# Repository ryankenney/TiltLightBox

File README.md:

TiltLightBox
====================

About
--------------------

TiltLightBox is a hardware/software platform we developed for an ( link) interactive exhibit at Burning Man 2015. At its core, TiltLightBox is just a bunch of durable, illuminated boxes that can detect when they're knocked over and respond with appropriate color/sound effects. They employ battery packs and cheap wifi adapters in order to centralized control of color/sound themes.

[![alt text][1]][2]

  [1]: docs/Overview_thumb.png (Overview)
  [2]: docs/Overview.png

[![alt text][3]][4]

  [3]: docs/Overview_TiltLightBox_thumb.png (TiltLightBox Unit)
  [4]: docs/Overview_TiltLightBox.png

[![alt text][5]][6]

  [5]: docs/Overview_TiltLightBox-Server_thumb.png (TiltLightBox Server)
  [6]: docs/Overview_TiltLightBox-Server.png

Index
--------------------

*  [Building the Hardware]()
	* [Wiring Diagrams](docs/Wiring Diagrams.md)
*  [Testing in Web Emulator]()
* [Deploying the TiltLightBox Software to the Arduino Boxes](docs/Arduino Setup.md) (to Arduinos)
* [Deploying the TiltLightBox Software to the Raspberry Pi Server](docs/Raspberry Pi Setup.md) (to Raspberry Pi)
* [Archive](archive/README.md)

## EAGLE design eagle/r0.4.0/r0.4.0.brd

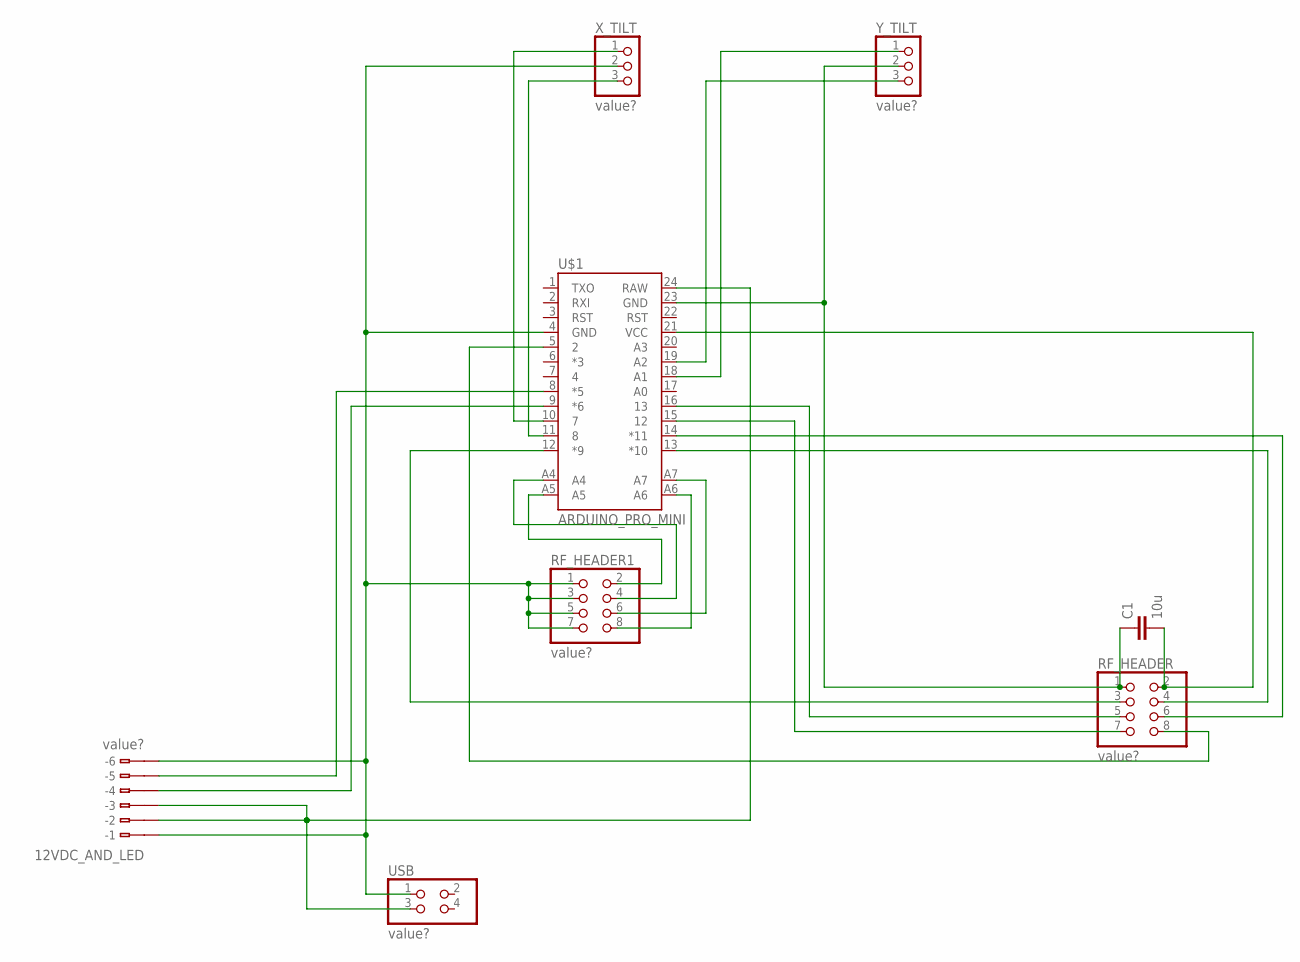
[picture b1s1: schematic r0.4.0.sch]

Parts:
12VDC_AND_LED: value?; 234-206
C1: 10u; CAP-PTH-SMALL
RF_HEADER, RF_HEADER1: value?; 2X04
U$1: ARDUINO_PRO_MINI
USB: value?; 2X02
X_TILT: value?; 1X03
Y_TILT: value?; 1X03

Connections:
unnamed: U$1.10 (7), X_TILT.1
unnamed: 12VDC_AND_LED.B1 (B-1), 12VDC_AND_LED.B6 (B-6), RF_HEADER1.1, RF_HEADER1.3, RF_HEADER1.5, RF_HEADER1.7, U$1.4 (GND), USB.1, X_TILT.2
unnamed: U$1.11 (8), X_TILT.3
unnamed: 12VDC_AND_LED.B5 (B-5), U$1.8 (*5)
unnamed: 12VDC_AND_LED.B2 (B-2), 12VDC_AND_LED.B3 (B-3), U$1.24 (RAW), USB.3
unnamed: C1.1, RF_HEADER.1, U$1.23 (GND), Y_TILT.2
unnamed: 12VDC_AND_LED.B4 (B-4), U$1.9 (*6)
unnamed: RF_HEADER1.4, U$1.A4
unnamed: U$1.19 (A2), Y_TILT.3
unnamed: RF_HEADER.3, U$1.12 (*9)
unnamed: RF_HEADER.4, U$1.13 (*10)
unnamed: RF_HEADER.6, U$1.14 (*11)
unnamed: RF_HEADER1.2, U$1.A5
unnamed: RF_HEADER1.8, U$1.A6
unnamed: RF_HEADER1.6, U$1.A7
unnamed: RF_HEADER.7, U$1.15 (12)
unnamed: RF_HEADER.5, U$1.16 (13)
unnamed: RF_HEADER.8, U$1.5 (2)
unnamed: U$1.18 (A1), Y_TILT.1
Y_TILT: C1.2, RF_HEADER.2, U$1.21 (VCC)

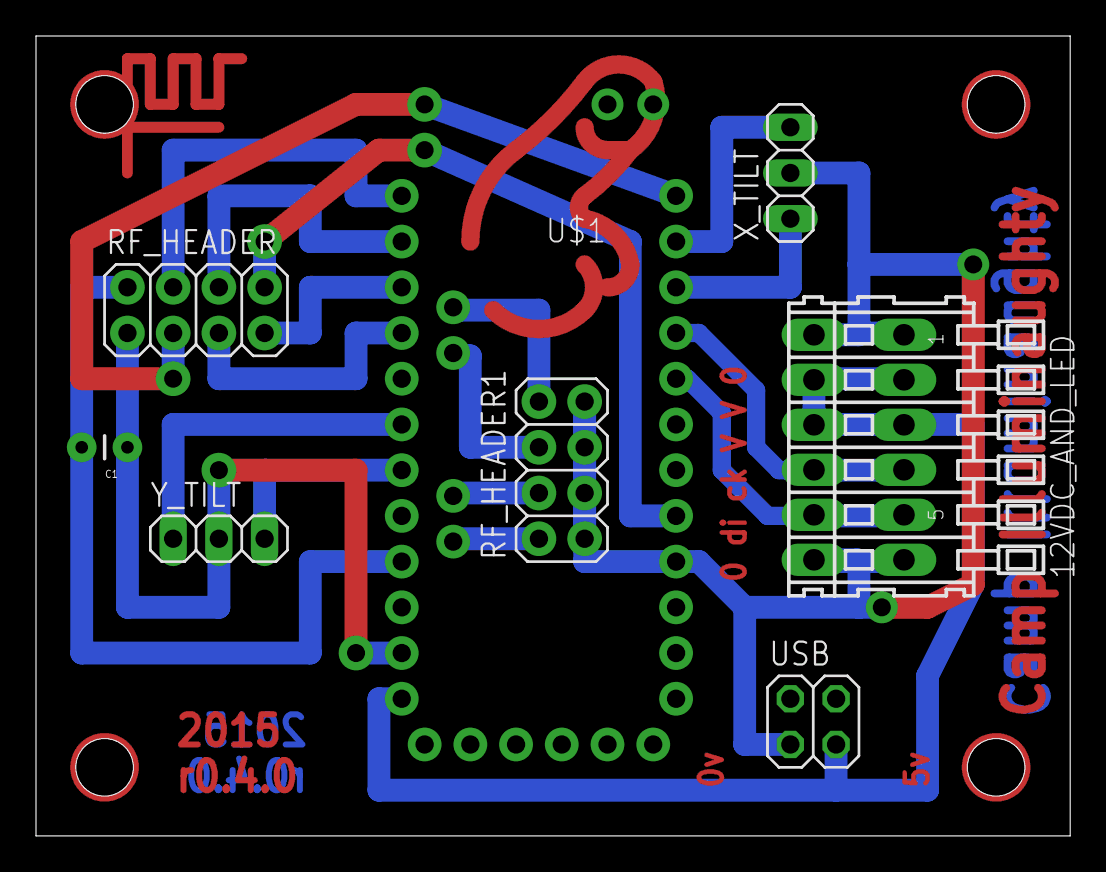
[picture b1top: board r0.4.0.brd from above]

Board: 2 copper layers, 57.5 x 44.4 mm, 8 parts (0 on the bottom side), 20 nets.

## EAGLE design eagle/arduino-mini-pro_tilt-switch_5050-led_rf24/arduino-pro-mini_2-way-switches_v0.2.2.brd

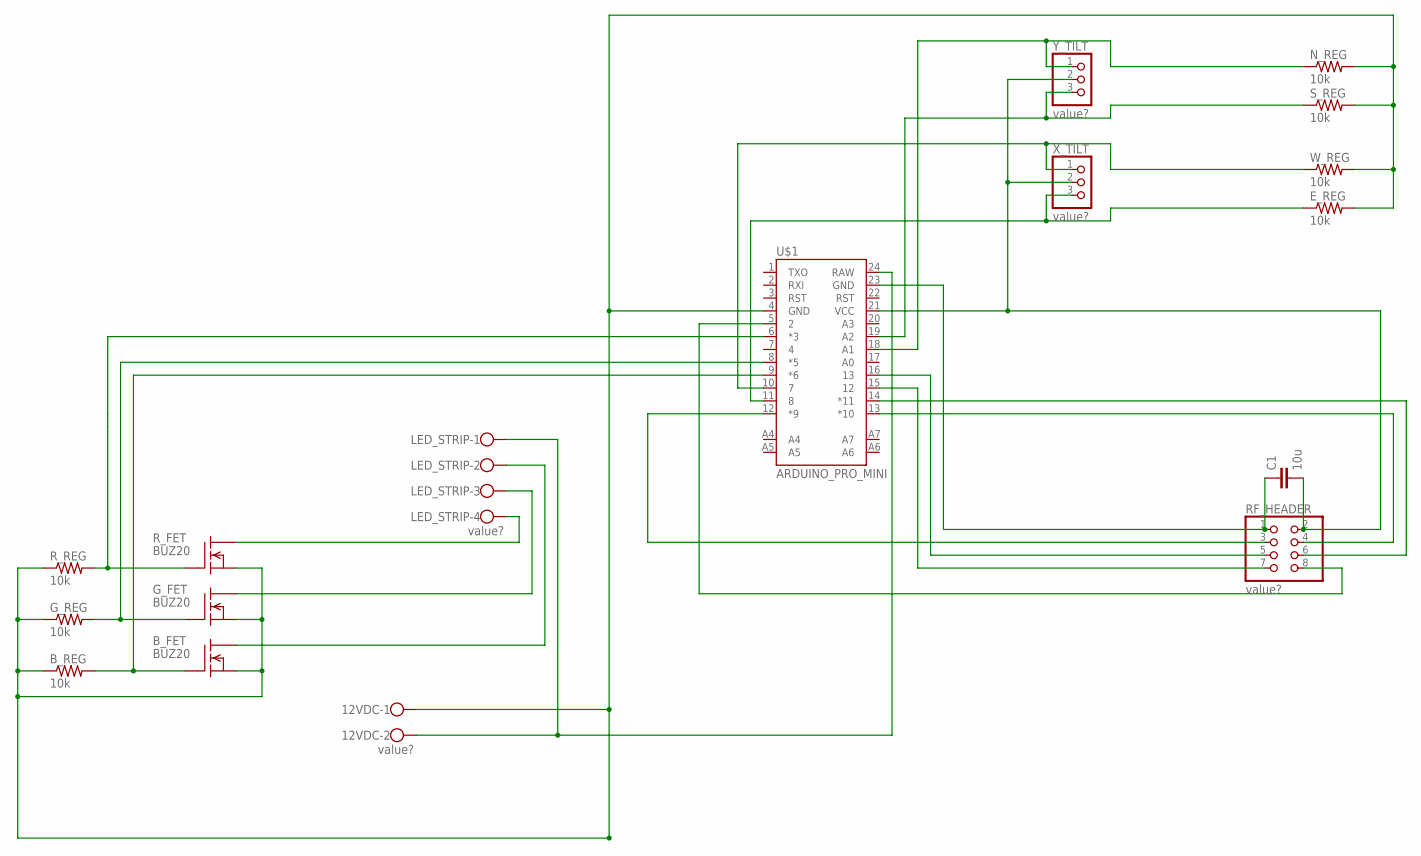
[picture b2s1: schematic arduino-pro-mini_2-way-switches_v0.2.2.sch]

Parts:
12VDC: value?; W237-102
B_FET: BUZ20; TO220
B_REG: 10k; AXIAL-0.4
C1: 10u; CAP-PTH-SMALL
E_REG: 10k; AXIAL-0.4
G_FET: BUZ20; TO220
G_REG: 10k; AXIAL-0.4
LED_STRIP: value?; W237-4
N_REG: 10k; AXIAL-0.4
RF_HEADER: value?; 2X04
R_FET: BUZ20; TO220
R_REG: 10k; AXIAL-0.4
S_REG: 10k; AXIAL-0.4
U$1: ARDUINO_PRO_MINI
W_REG: 10k; AXIAL-0.4
X_TILT: value?; 1X03
Y_TILT: value?; 1X03

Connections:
unnamed: U$1.10 (7), W_REG.P$1 (1), X_TILT.1
unnamed: B_FET.1 (G), B_REG.P$2 (2), U$1.9 (*6)
unnamed: R_FET.1 (G), R_REG.P$2 (2), U$1.6 (*3)
unnamed: G_FET.2 (D), LED_STRIP.3
unnamed: B_FET.2 (D), LED_STRIP.2
unnamed: E_REG.P$1 (1), U$1.11 (8), X_TILT.3
unnamed: LED_STRIP.4, R_FET.2 (D)
unnamed: 12VDC.2, LED_STRIP.1, U$1.24 (RAW)
unnamed: 12VDC.1, B_FET.3 (S), B_REG.P$1 (1), E_REG.P$2 (2), G_FET.3 (S), G_REG.P$1 (1), N_REG.P$2 (2), R_FET.3 (S), R_REG.P$1 (1), S_REG.P$2 (2), U$1.4 (GND), W_REG.P$2 (2)
unnamed: G_FET.1 (G), G_REG.P$2 (2), U$1.8 (*5)
unnamed: S_REG.P$1 (1), U$1.19 (A2), Y_TILT.3
unnamed: RF_HEADER.3, U$1.12 (*9)
unnamed: RF_HEADER.4, U$1.13 (*10)
unnamed: RF_HEADER.6, U$1.14 (*11)
unnamed: C1.1, RF_HEADER.1, U$1.23 (GND)
unnamed: RF_HEADER.7, U$1.15 (12)
unnamed: RF_HEADER.5, U$1.16 (13)
unnamed: RF_HEADER.8, U$1.5 (2)
unnamed: N_REG.P$1 (1), U$1.18 (A1), Y_TILT.1
Y_TILT: C1.2, RF_HEADER.2, U$1.21 (VCC), X_TILT.2, Y_TILT.2

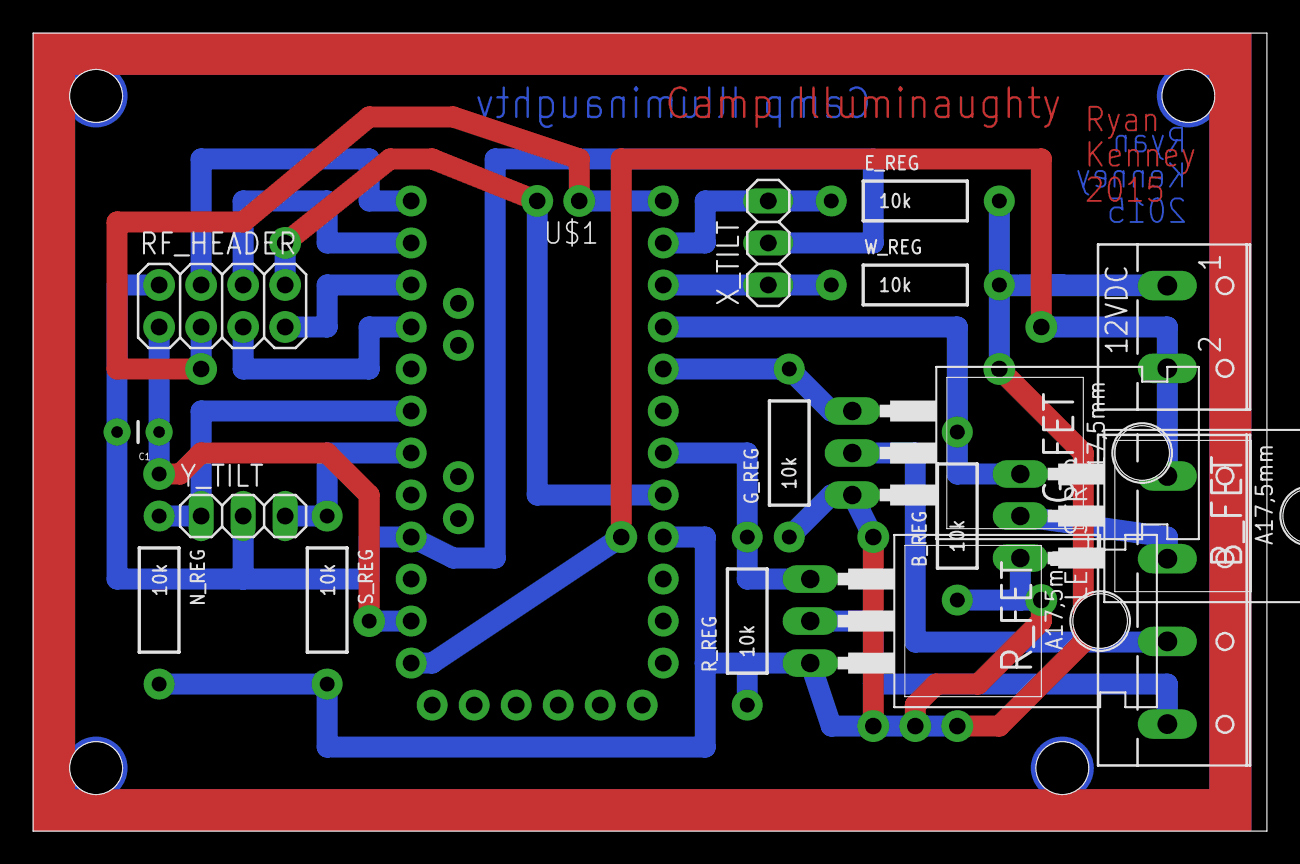
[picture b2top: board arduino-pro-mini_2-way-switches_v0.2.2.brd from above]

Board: 2 copper layers, 74.6 x 48.2 mm, 17 parts (0 on the bottom side), 20 nets.

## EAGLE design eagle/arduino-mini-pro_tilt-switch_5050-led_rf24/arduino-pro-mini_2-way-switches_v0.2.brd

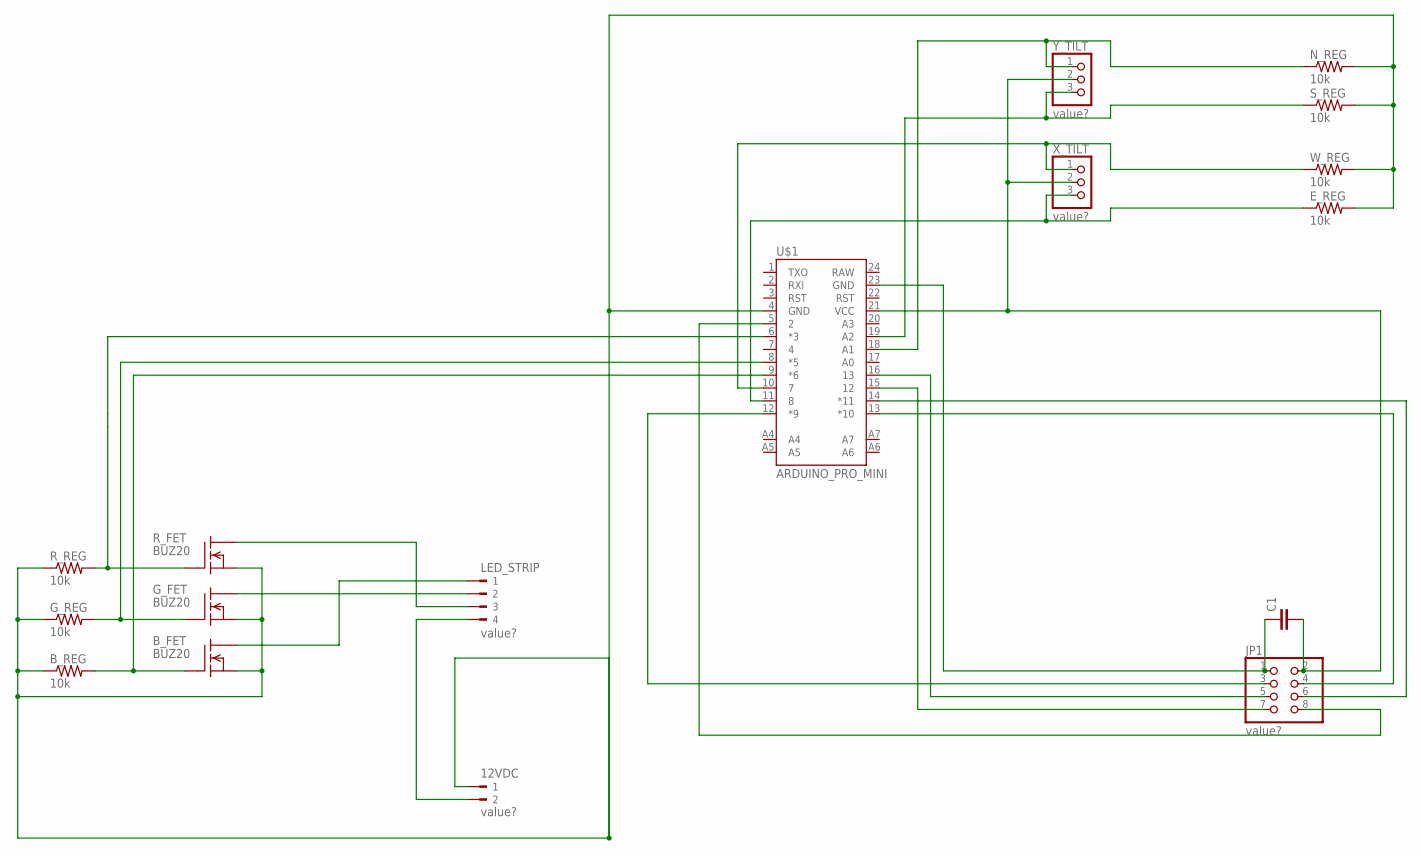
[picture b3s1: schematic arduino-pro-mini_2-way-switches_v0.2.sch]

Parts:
12VDC: value?; 180-2
B_FET: BUZ20; TO220
B_REG: 10k; AXIAL-0.4
C1: CAPPTH; CAP-PTH-SMALL
E_REG: 10k; AXIAL-0.4
G_FET: BUZ20; TO220
G_REG: 10k; AXIAL-0.4
JP1: value?; 2X04
LED_STRIP: value?; 180-4
N_REG: 10k; AXIAL-0.4
R_FET: BUZ20; TO220
R_REG: 10k; AXIAL-0.4
S_REG: 10k; AXIAL-0.4
U$1: ARDUINO_PRO_MINI
W_REG: 10k; AXIAL-0.4
X_TILT: value?; 1X03
Y_TILT: value?; 1X03

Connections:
unnamed: U$1.10 (7), W_REG.P$1 (1), X_TILT.1
unnamed: B_FET.1 (G), B_REG.P$2 (2), U$1.9 (*6)
unnamed: R_FET.1 (G), R_REG.P$2 (2), U$1.6 (*3)
unnamed: B_FET.2 (D), LED_STRIP.1
unnamed: E_REG.P$1 (1), U$1.11 (8), X_TILT.3
unnamed: LED_STRIP.3, R_FET.2 (D)
unnamed: G_FET.2 (D), LED_STRIP.2
unnamed: 12VDC.2, LED_STRIP.4
unnamed: 12VDC.1, B_FET.3 (S), B_REG.P$1 (1), E_REG.P$2 (2), G_FET.3 (S), G_REG.P$1 (1), N_REG.P$2 (2), R_FET.3 (S), R_REG.P$1 (1), S_REG.P$2 (2), U$1.4 (GND), W_REG.P$2 (2)
unnamed: C1.1, JP1.1, U$1.23 (GND)
unnamed: G_FET.1 (G), G_REG.P$2 (2), U$1.8 (*5)
unnamed: S_REG.P$1 (1), U$1.19 (A2), Y_TILT.3
unnamed: JP1.3, U$1.12 (*9)
unnamed: JP1.4, U$1.13 (*10)
unnamed: JP1.6, U$1.14 (*11)
unnamed: JP1.7, U$1.15 (12)
unnamed: JP1.5, U$1.16 (13)
unnamed: JP1.8, U$1.5 (2)
unnamed: N_REG.P$1 (1), U$1.18 (A1), Y_TILT.1
Y_TILT: C1.2, JP1.2, U$1.21 (VCC), X_TILT.2, Y_TILT.2

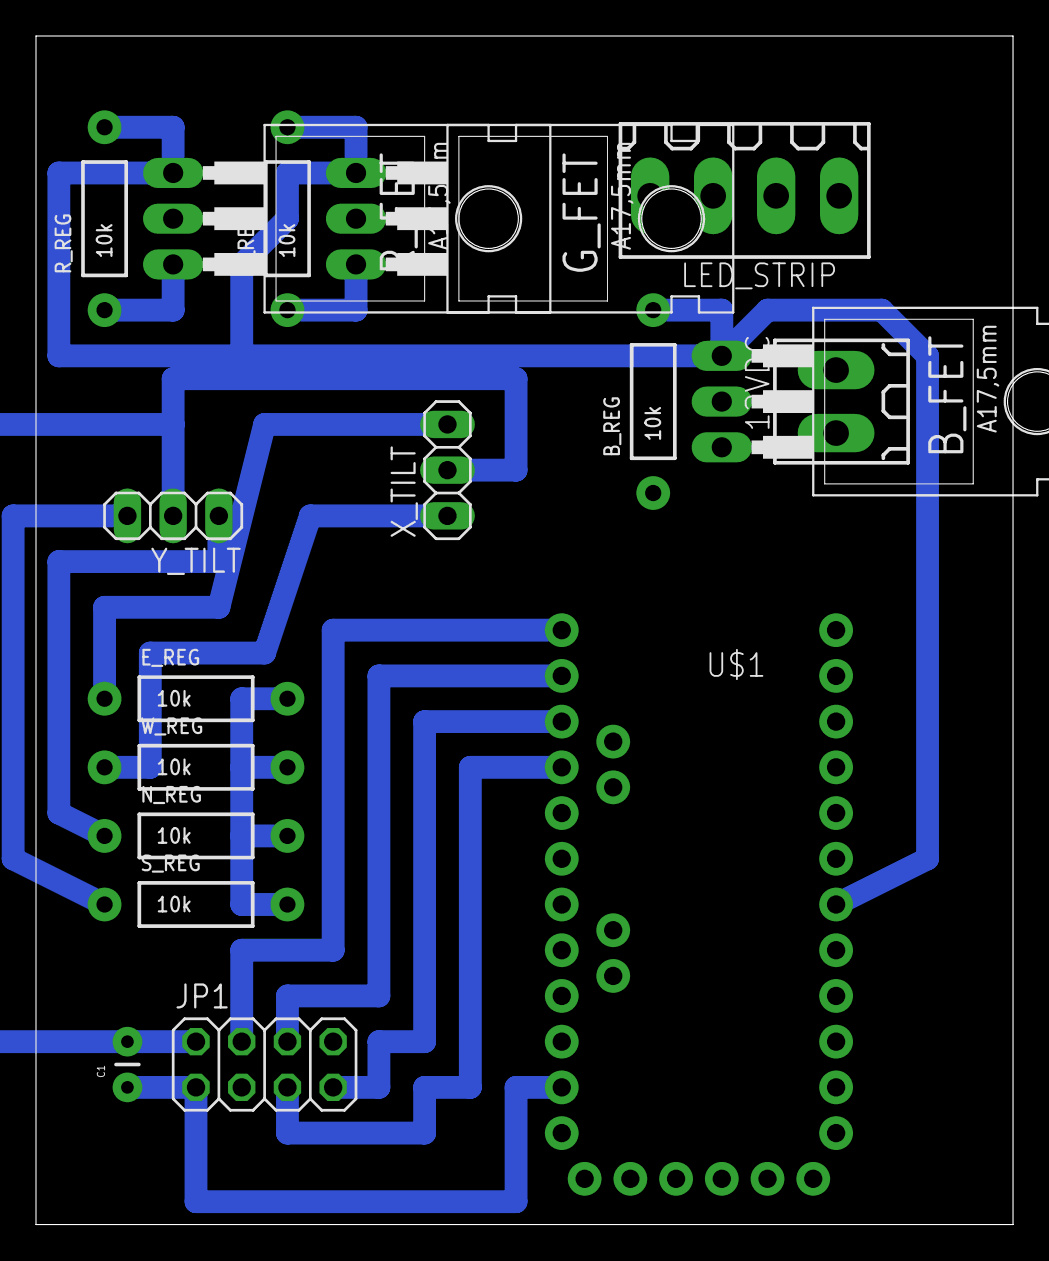
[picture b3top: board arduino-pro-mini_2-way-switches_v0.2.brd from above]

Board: 2 copper layers, 54.3 x 66.0 mm, 17 parts (0 on the bottom side), 20 nets.

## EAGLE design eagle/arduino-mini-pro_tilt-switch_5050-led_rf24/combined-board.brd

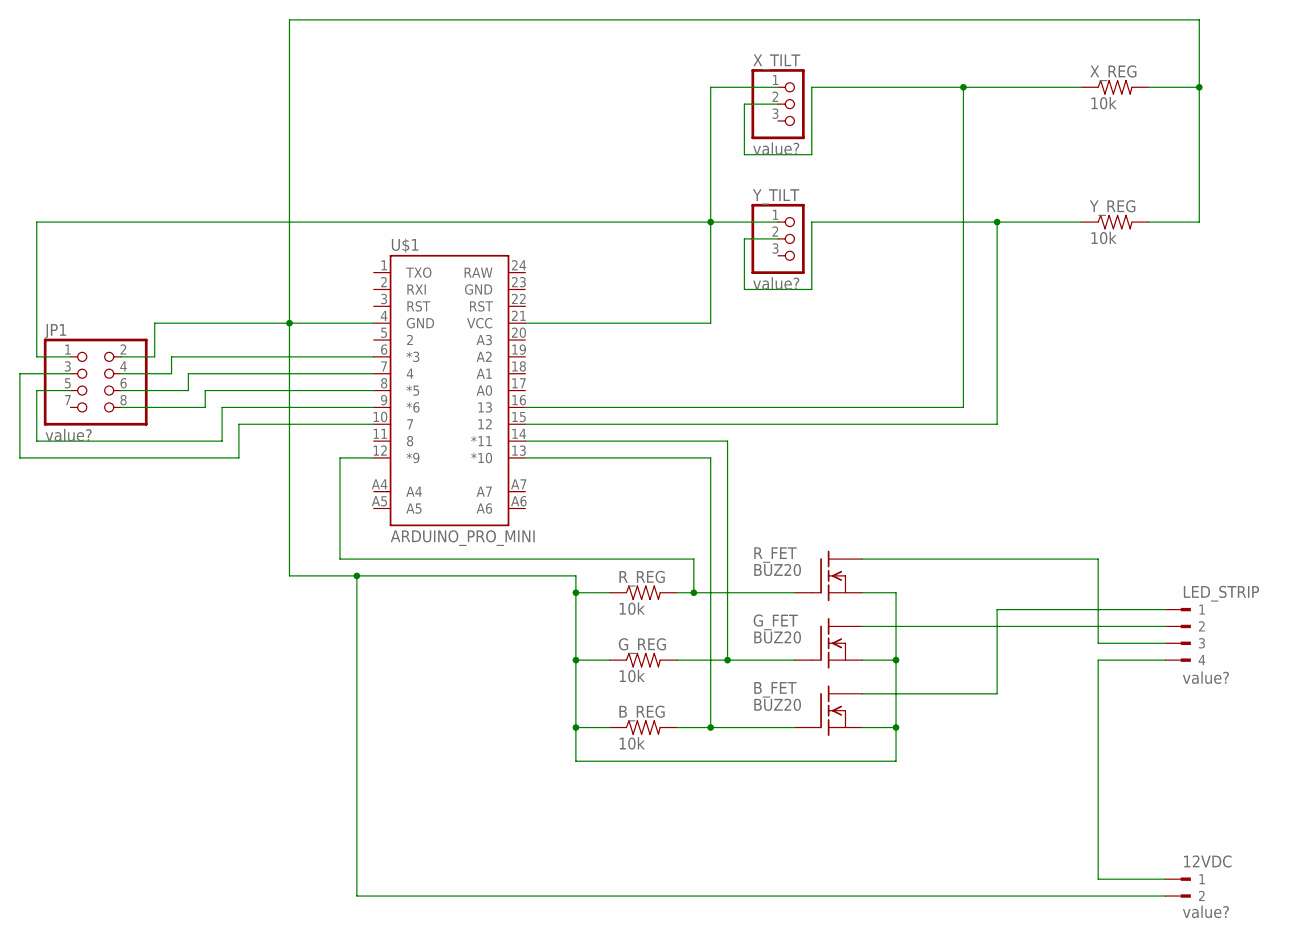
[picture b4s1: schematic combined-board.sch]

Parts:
12VDC: value?; 180-2
B_FET: BUZ20; TO220
B_REG: 10k; AXIAL-0.4
G_FET: BUZ20; TO220
G_REG: 10k; AXIAL-0.4
JP1: value?; 2X04
LED_STRIP: value?; 180-4
R_FET: BUZ20; TO220
R_REG: 10k; AXIAL-0.4
U$1: ARDUINO_PRO_MINI
X_REG: 10k; AXIAL-0.4
X_TILT: value?; 1X03
Y_REG: 10k; AXIAL-0.4
Y_TILT: value?; 1X03

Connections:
unnamed: U$1.16 (13), X_REG.P$1 (1), X_TILT.2
unnamed: B_FET.1 (G), B_REG.P$2 (2), U$1.13 (*10)
unnamed: R_FET.1 (G), R_REG.P$2 (2), U$1.12 (*9)
unnamed: B_FET.2 (D), LED_STRIP.1
unnamed: U$1.15 (12), Y_REG.P$1 (1), Y_TILT.2
unnamed: LED_STRIP.3, R_FET.2 (D)
unnamed: G_FET.2 (D), LED_STRIP.2
unnamed: 12VDC.1, LED_STRIP.4
unnamed: 12VDC.2, B_FET.3 (S), B_REG.P$1 (1), G_FET.3 (S), G_REG.P$1 (1), JP1.2, R_FET.3 (S), R_REG.P$1 (1), U$1.4 (GND), X_REG.P$2 (2), Y_REG.P$2 (2)
unnamed: JP1.5, U$1.9 (*6)
unnamed: G_FET.1 (G), G_REG.P$2 (2), U$1.14 (*11)
unnamed: JP1.4, U$1.6 (*3)
unnamed: JP1.6, U$1.7 (4)
unnamed: JP1.8, U$1.8 (*5)
unnamed: JP1.3, U$1.10 (7)
Y_TILT: JP1.1, U$1.21 (VCC), X_TILT.1, Y_TILT.1

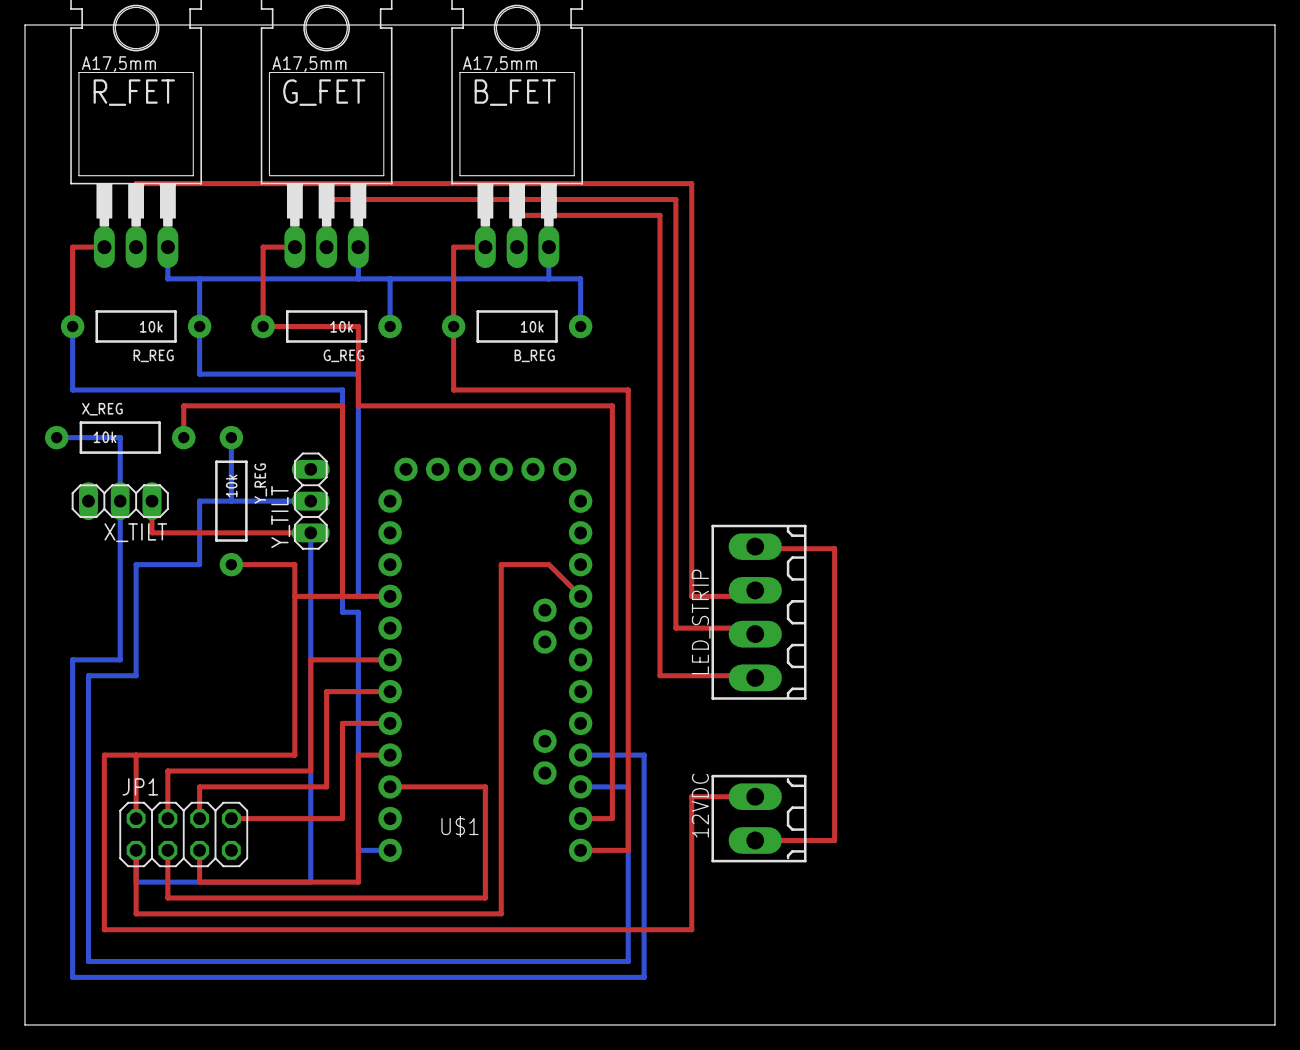
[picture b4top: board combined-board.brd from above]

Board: 2 copper layers, 100.0 x 80.0 mm, 14 parts (0 on the bottom side), 16 nets.

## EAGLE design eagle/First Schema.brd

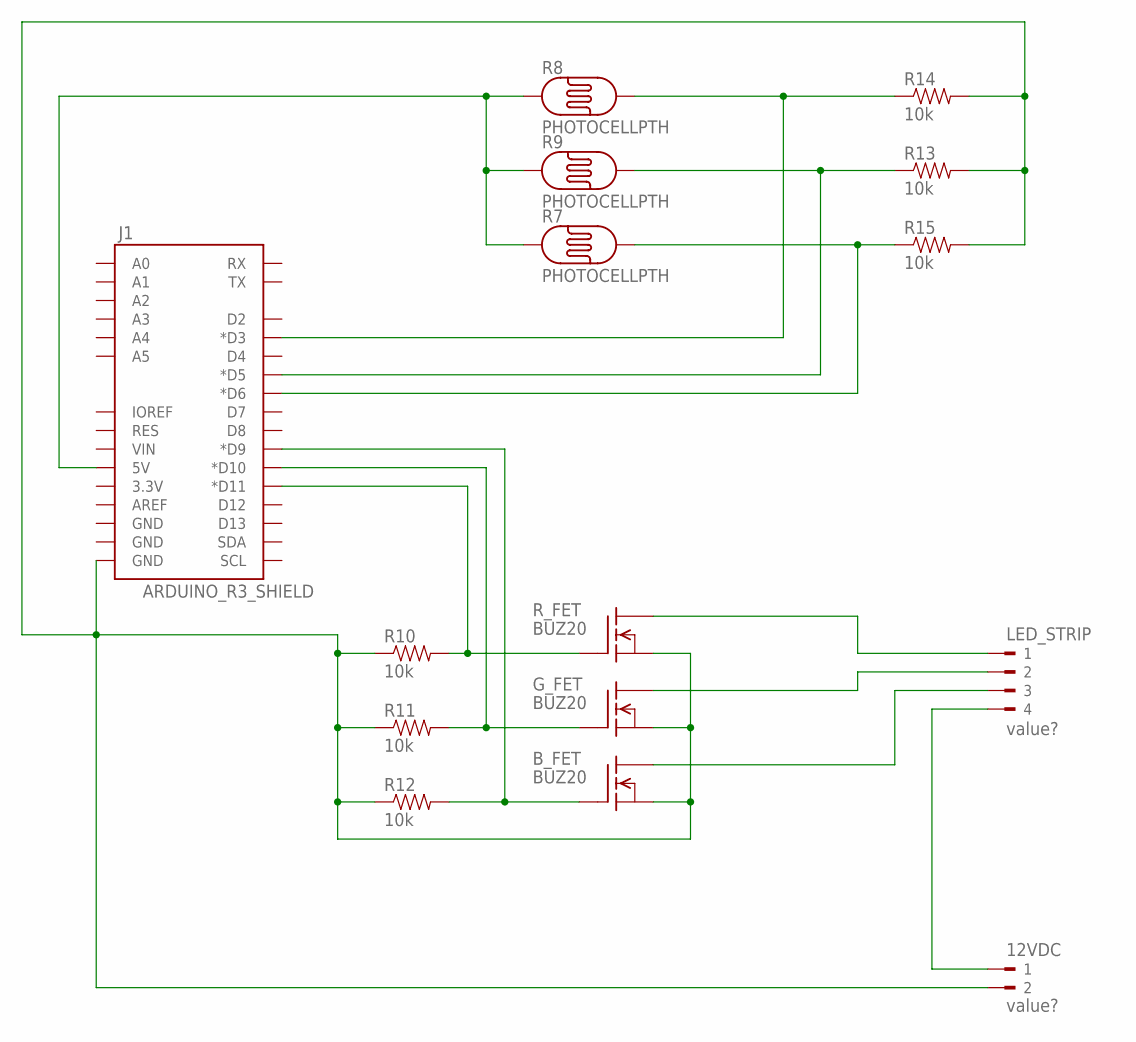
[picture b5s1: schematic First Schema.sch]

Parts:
12VDC: value?; 180-2
B_FET: BUZ20; TO220
G_FET: BUZ20; TO220
J1: ARDUINO_R3_SHIELD; UNO_R3_SHIELD
LED_STRIP: value?; 180-4
R7, R8, R9: PHOTOCELLPTH; PHOTOCELL
R10, R11, R12, R13, R14, R15: 10k; AXIAL-0.4
R_FET: BUZ20; TO220

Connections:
unnamed: J1.D11 (*D11), R10.P$2 (2), R_FET.1 (G)
unnamed: B_FET.1 (G), J1.D9 (*D9), R12.P$2 (2)
unnamed: J1.5V, R7.1, R8.1, R9.1
unnamed: B_FET.2 (D), LED_STRIP.3
unnamed: J1.D3 (*D3), R8.2, R14.P$1 (1)
unnamed: LED_STRIP.1, R_FET.2 (D)
unnamed: G_FET.2 (D), LED_STRIP.2
unnamed: 12VDC.1, LED_STRIP.4
unnamed: 12VDC.2, B_FET.3 (S), G_FET.3 (S), J1.GND@0 (GND), R10.P$1 (1), R11.P$1 (1), R12.P$1 (1), R13.P$2 (2), R14.P$2 (2), R15.P$2 (2), R_FET.3 (S)
unnamed: J1.D5 (*D5), R9.2, R13.P$1 (1)
unnamed: J1.D6 (*D6), R7.2, R15.P$1 (1)
unnamed: G_FET.1 (G), J1.D10 (*D10), R11.P$2 (2)

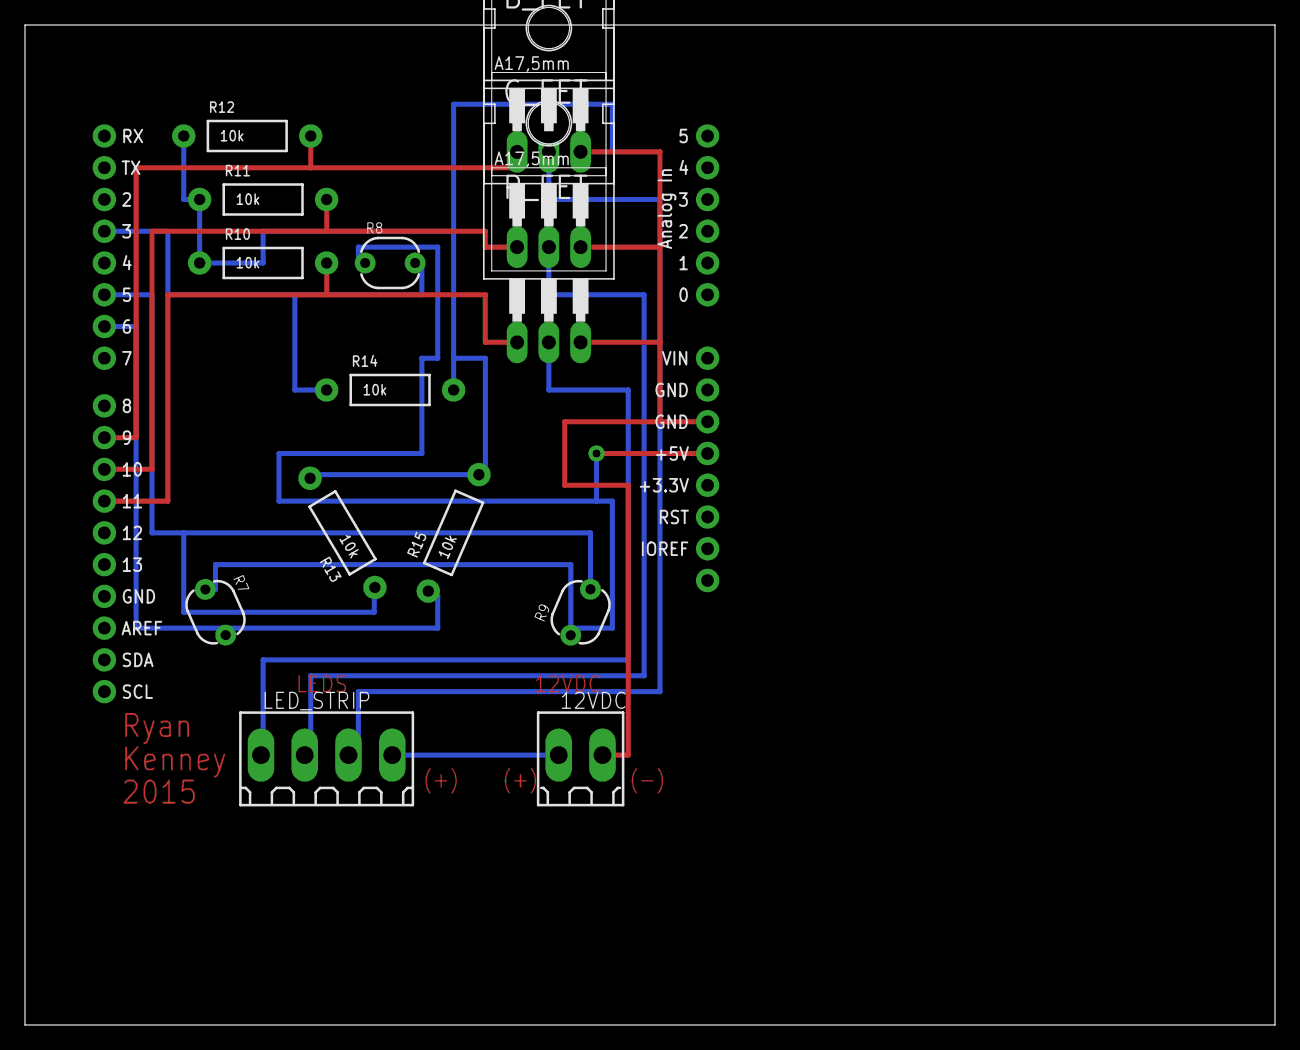
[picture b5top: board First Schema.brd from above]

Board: 2 copper layers, 100.0 x 80.0 mm, 15 parts (0 on the bottom side), 12 nets.

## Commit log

2015-05-04 Added initial versions of arduino sketch, fritzing wiring diagram, and eagle pcb layout
2015-05-04 Added arduino-mini-pro_tilt-switch_5050-led_rf24
2015-05-09 Added combined-board_external-wires brd/sch * Uses arduino mini pro * Second layer is option (could just be 5 wires) * Has known bugs
2015-05-12 * Added rf-header library * Added a couple of versions of the board
2015-05-17 Added arduino sketches: * color_change_demo * tilt-switch-5050_controller
2015-05-17 Added readme
2015-05-17 Removed old tilt switch sketch (3 switches)
2015-05-17 Added arduino sketch for RF sender/receiver
2015-05-18 * Added several revisions of the board--including the version submitted for printing. * Added my own MOSFET library
2015-05-23 Added initial attempt at a js/arduino cross-compiled library
2015-05-23 Added a native JS color cycling demo
2015-05-23 Added missing html file
2015-05-24 Added next steps in breaking lib up. Currently has a runtime error.
2015-05-25 * Cleaned up the interface between JS and C * Changed from C to CPP files in order to use JS callback methods with Emscripten
2015-05-25 HTML fixes for the last commit
2015-05-25 Removed color_generator.js (it's a transient file)
2015-05-26 * Made timing info clock-based as opposed to cycle-based * Started laying the groundwork for swappable color algorithms
2015-05-26 * Pushed fire alg into separate cpp file * Added second phase (yellow) to fire alg * Added support for random values (implementation needs to be injected)
2015-05-26 Tweaked color
2015-05-26 Added campfire audio
2015-05-28 * Refactored fire_alg into a more generic internal mechanisms * Added swappable sleep() function. Not used yet. * Added .gitignore for color_generator.js
2015-05-28 * Finished extracting generic color transitions into color_phase * Renamed "fire alg" to "purple calm alg" (fire needs a mechnism for random)
2015-06-02 Adjusted tilt sketch to use inverted values (pull-up resistors)
2015-06-10 Added state-based (standing/tilting/tilted) patterns
2015-06-11 Added automatic roll from TILTING to TILTED states
2015-06-12 Added clickable interaction to demo html page
2015-06-13 Reorganized js demo project into submodules
2015-06-15 Added first sketch using the tilt_light_box library
2015-06-16 Minor code cleanup
2015-06-26 * Added a second color alg, "disco" * Added jquery to the webpage
2015-06-26 Tweaked box layout a bit in the demo html
2015-06-29 Tied tilt sensors to tilt_light_box library usage. Tweaked colors a bit.
2015-06-29 Added RF reading for theme changes
2015-06-29 * Added RF notification of tilt to tilt_light_box.ino * Added box initialization at creation time to tilt_light_box.cpp * Shifted constant values in tilt_light_box.h
2015-07-06 * Removed debug delay and oversized arrays from tilt_light_box.ino * Added sender/receiver demos for theme change and tilt listening
2015-07-06 Renamed tilt_light_box to tilt-light-box
2015-07-06 Moved tilt-light-box to tiltlightbox (the arduino ide is piiiicky)
2015-07-06 * Added interrupted-based ACK read to tiltlightbox_arduino_theme_sender * A couple more file renames for arduino
2015-07-06 Array sizing fix in tiltlightbox.ino
2015-07-07 Fixing LED pin assignments. Switching to nRF24L01 RF library. Updating while loop use use different read semantics.
2015-07-07 Adding sample state change from USB signal
2015-07-07 * Added centralized cycle function to tilt_light_box.cpp * Added partial integration with the html demo * Did not integrate with tiltlightbox.ino
2015-07-08 Finished integrating centralized cycle function with html demo
2015-07-26 * Added a README.md with overview info * Added a git submodule pointing to the RF24 lib we're using
2015-07-26 * Added all of the new tilt_light_box.h callbacks to tiltlightbox.ino * Tweaked the tiltlightbox.ino radio configuration to better match the node.js usage * Updated tiltlightbox_arduino_tilt_listener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
2015-07-27 * Fixed conflicting includes in tiltlightbox.ino ** Was preventing proper transmit to tiltlightbox_arduino_theme_sender.ino * Updated tiltlightbox_arduino_theme_sender.ino to work with the latest til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
2015-07-28 * Started creating board v0.4, which supports usb-power and addressable LEDs
2015-07-28 Added board r0.2.6, which is the one I ordered in the first official prints of
2015-07-28 * Updated tiltlightbox.ino to work with our addressable 5v leds * Fixed the radio reading loop
2015-07-29 Added finishing touches to r0.4.0 of the board
2015-07-29 Updated r0.4.0 of the board: * Thickened usb header pads * Added a couple of pads for unused pins
2015-08-03 Added simple demos of Raspberry Pi sound and radio usage
2015-08-19 Tweaked main .ino to work with with a broadcast
2015-08-19 Added server samples that work with broadcast to multiple boxes
2015-08-28 Just a snapshot of where we're at
2015-08-30 Added .gitignore for node_modules
2015-08-30 Adding all nodejs/raspberry pi files generated at Burning Man
2015-10-24 Committing what I had on my laptop after the last deployment to the Arduinos at Burning Man. It's been a while, but it looks like the web page needs fixing at a minimum.
2015-10-24 Added some documentation
2015-10-24 Tweaked "FIXME" rendering in docs
2015-10-24 Tweaked fixme image
2015-10-24 Documentation tweak
2015-10-24 Notes update
2015-10-24 Docs update
2015-10-24 Updated TODOs
2015-10-25 Docs updates
2015-10-25 Reorganized docs file structure
2015-10-25 Trying out new image reference in docs
2015-10-25 Tweaked image link
2015-10-25 Reorganized arduino sketches directory structure
2015-10-26 Updated docs
2015-10-27 Removed all extra/old Node.js programs
2015-10-27 More cleanup... * Deleted unused node prog Button.js * Deleted log file * Deleted gitmodule RF24 (opting for manual load vi README.md) * Moved fixme.xcf into docs
2015-10-27 Archived arduino-uno-tilt-switch-5050-controller-shield.fzz
2015-10-27 Deleting old eagle sketches
2015-10-27 Archived the r0.2.6 eagle board
2015-10-29 Moved eagle board r0.4.0 to the archive
2015-10-29 Updating docs
2017-07-16 * Added node project definition * Added BowlingScore
2017-07-17 Minor docs update
2017-07-26 Added demonstration of random box ID
2017-07-26 Renamed arduino project to TiltLightBoxPin
2017-07-26 Renamed node to TileLightBoxServer
2017-07-26 Fixed previous dir rename
2017-07-26 Added initial 7-segment writing code
2017-07-26 Added reading of score from serial
2017-07-30 Broken node server up into pieces and applied ES6
2017-07-30 Fixed typo
2017-07-30 Added logging
2017-07-31 Tweaked logging
2017-07-31 Fixed radio binding
2017-07-31 Replaced main TiltLightBoxServer.js
2017-07-31 Added package-lock.json (snapshot of deps when installed on an rasp pi)
2017-08-03 * Added randomize of seed (not actually used right now, but could be) * Added encoding of tilt state with box ID, in an 8-bit packet
2017-08-03 Added transmission of tilting and resetting states
2017-08-03 Added score tracking per tilt state changes

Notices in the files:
parts and their libraries:
SparkFun-Boards: Licensing: Creative Commons ShareAlike 4.0 International - https://creativecommons.org/licenses/by-sa/4.0
